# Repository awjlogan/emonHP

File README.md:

# emonHP - Heat Pump Monitoring

## Introduction

_emonHP_ is a system for monitoring heat pump operation. It is designed to work with [OpenEnergyMonitor](https://openenergymonitor.org), but can be used as a standalone system.

The system provides the following interfaces:

- MBUS
- RS485
- AC sense
- OneWire
- USB-C
- 40-pin Raspberry Pi header

## Getting started

### Getting a board

- Purchase a heat pump monitoring system from the [OpenEnergyMonitor Shop](https://shop.openenergymonitor.com/)
- Build your own!
  - With [KiCad](https://www.kicad.org/) installed, run `./generate.py` in the `pcb` directory (tested on Linux and macOS only) to generate manufacturing files (KiCad PCB, Gerbers, BoM).

### emonHP

> [!NOTE]
Setting up as an integrated emonHP system requires a Raspberry Pi 4. This exposes extra UART ports on the 40-pin header which are not available on older versions.

Connect the Raspberry Pi to the 40 pin header.

> [!WARNING]
Power must only be applied to one of the emonHP's USB-C port *or* the Raspberry Pi's power port, never both.

### Standalone

Connect to a host computer through the USB-C port. The emonHP will enumerate as 3 serial ports.

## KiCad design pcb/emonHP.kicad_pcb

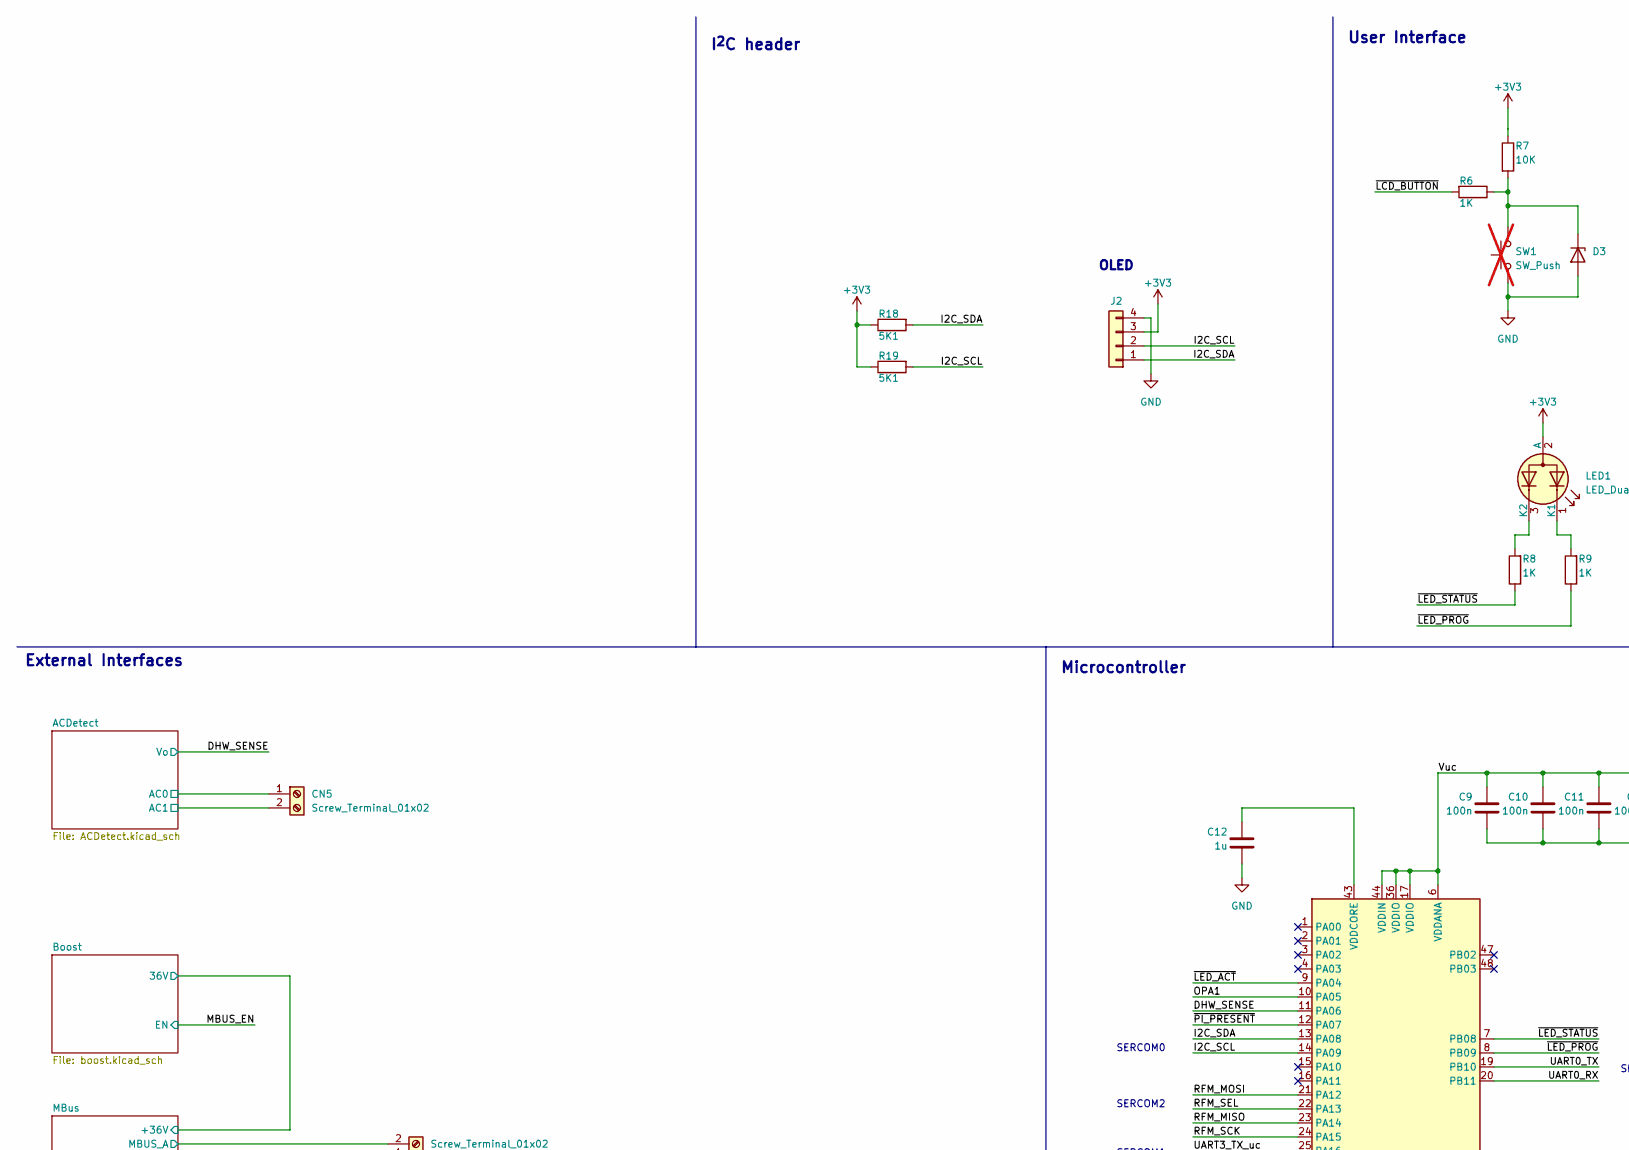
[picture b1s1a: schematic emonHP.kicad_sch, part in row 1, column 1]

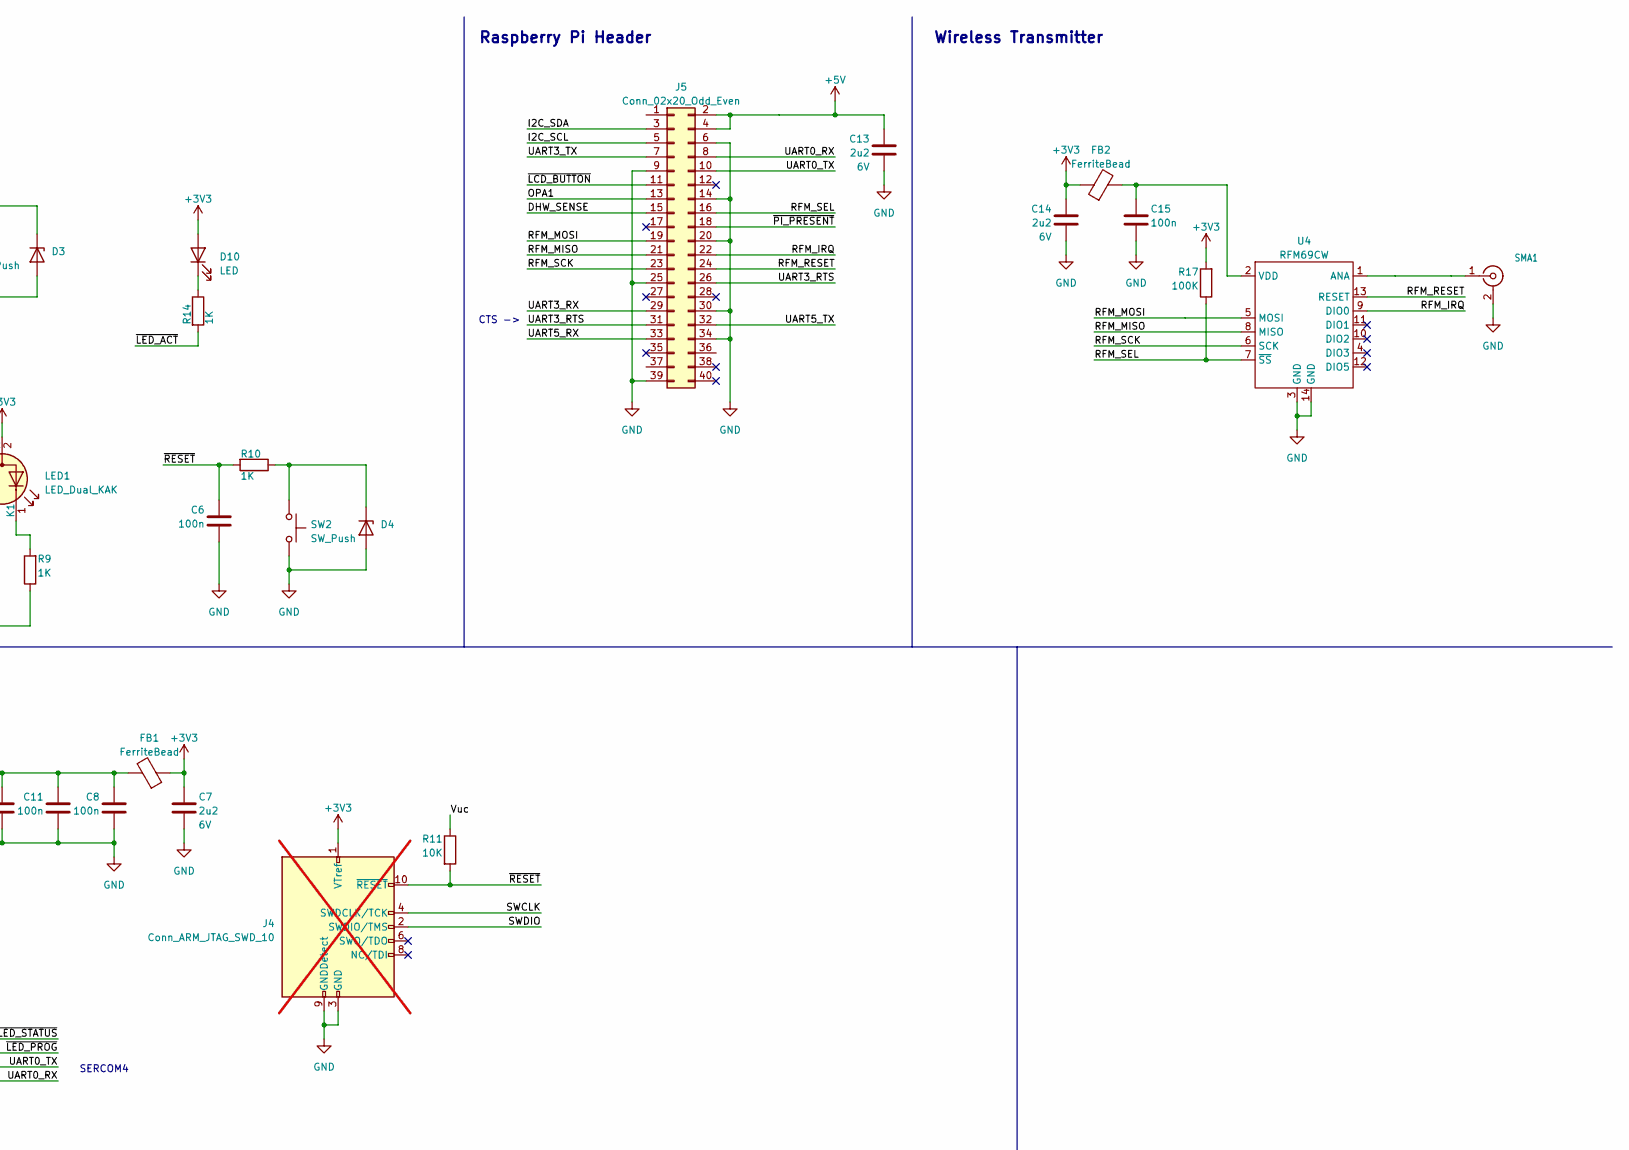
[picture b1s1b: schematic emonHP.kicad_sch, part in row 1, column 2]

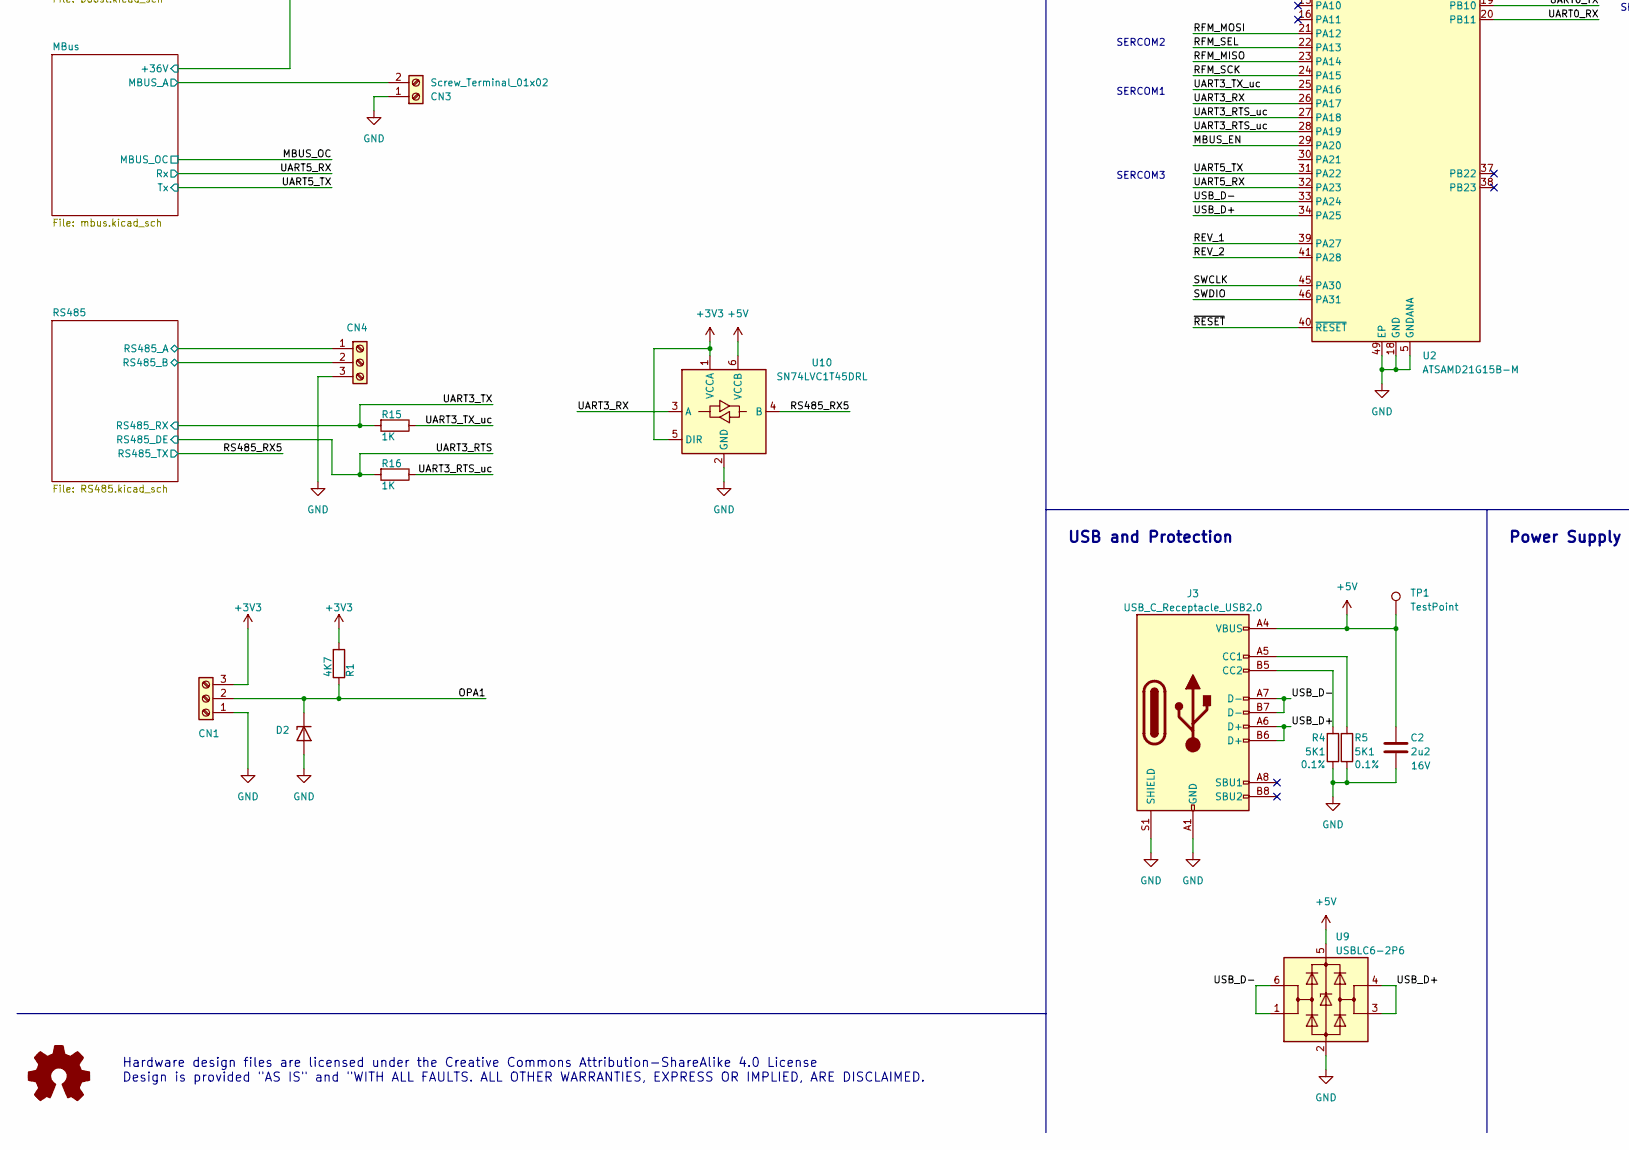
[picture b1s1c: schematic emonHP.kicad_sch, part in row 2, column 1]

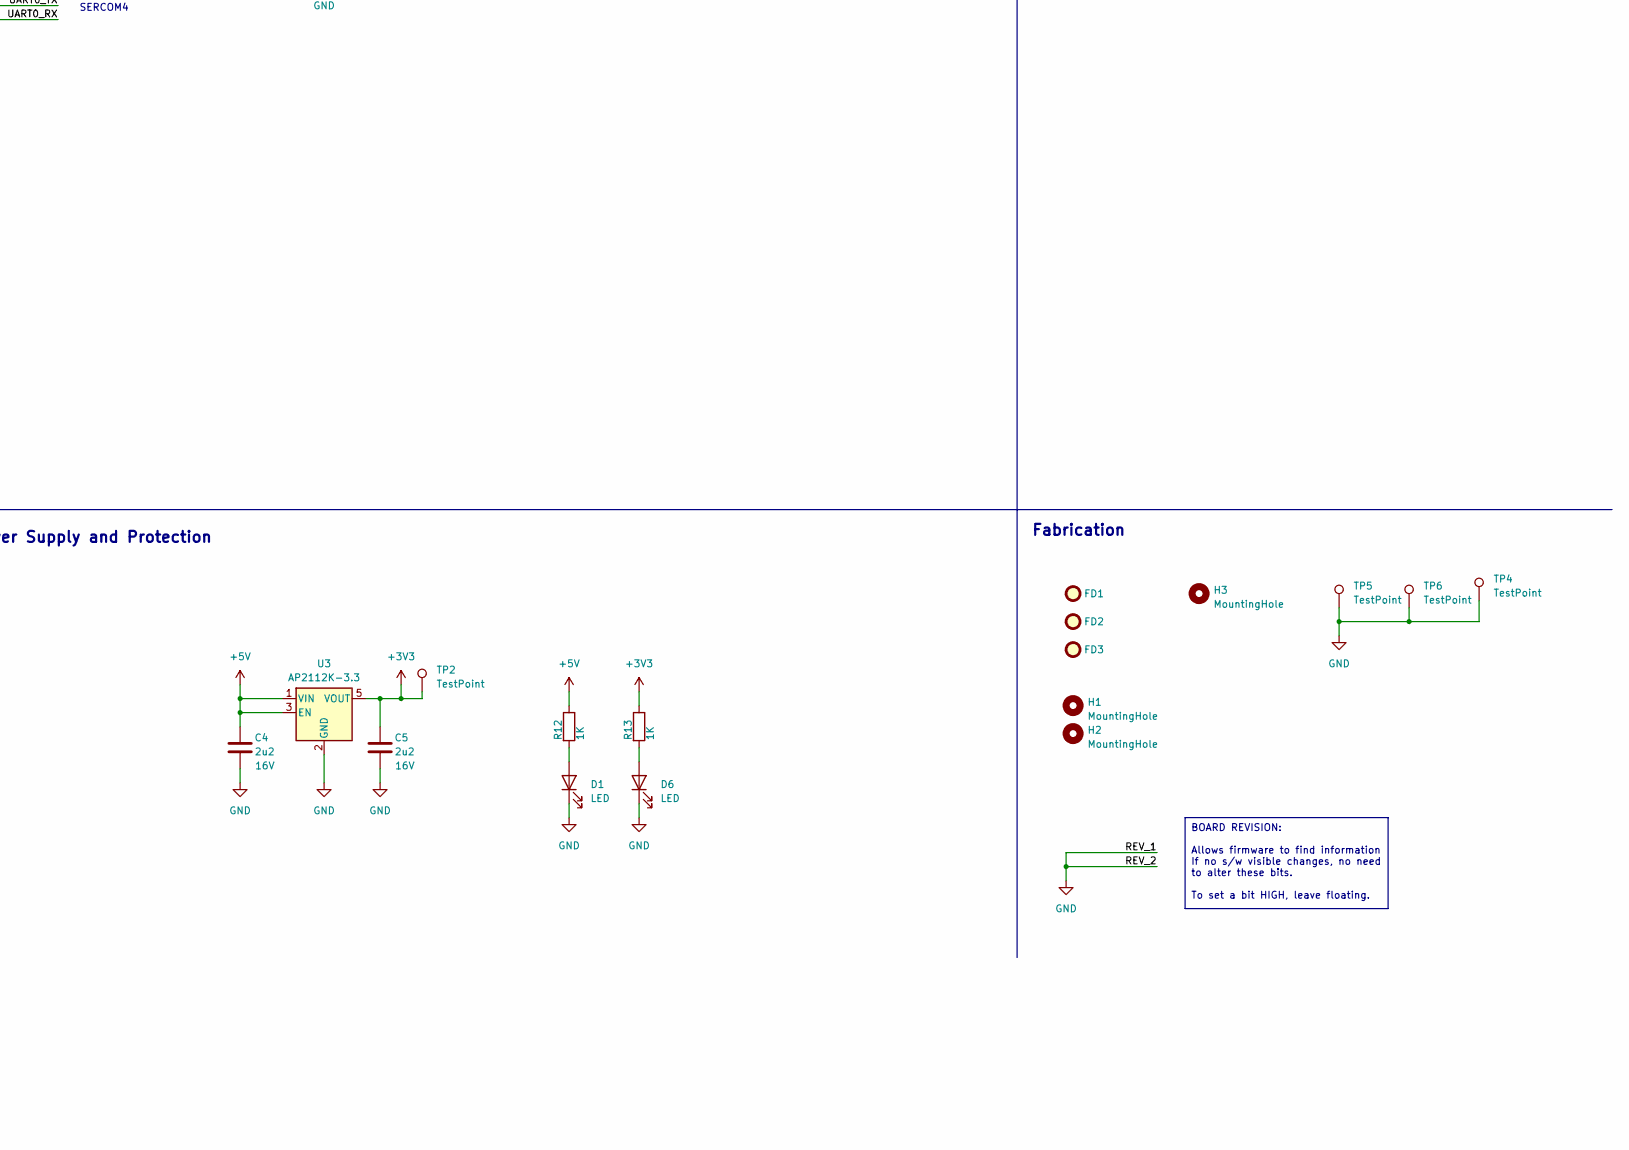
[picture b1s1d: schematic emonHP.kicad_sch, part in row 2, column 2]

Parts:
C2, C4, C5: 2u2; C_0603_1608Metric; Voltage 16V; LCSC C23630
C6, C8, C9, C10, C11, C15: 100n; C_0402_1005Metric; LCSC C1525
C7: 2u2; C_0603_1608Metric; Voltage 6V; LCSC C1525
C12: 1u; C_0402_1005Metric
C13, C14: 2u2; C_0603_1608Metric; Voltage 6V; LCSC C23630
CN1, CN4: CONN_03SCREW; TerminalBlock_Phoenix_PT-1,5-3-3.5-H_1x03_P3.50mm_Horizontal; MPN 5441359; Mouser 651-5441359
CN3: Screw_Terminal_01x02; TerminalBlock_Phoenix_PT-1,5-2-3.5-H_1x02_P3.50mm_Horizontal
CN5: Screw_Terminal_01x02; TerminalBlock_Phoenix_PT-1,5-2-5.0-H_1x02_P5.00mm_Horizontal
D1, D6, D10: LED; LED_0603_1608Metric; LCSC C2286
D2, D3, D4: ESD5Z3.3T5G; D_SOD-523
FB1, FB2: FerriteBead; R_0402_1005Metric
FD1, FD2, FD3: FIDUCIAL1X2; Fiducial_0.75mm_Mask1.5mm
H1, H2: MountingHole; MountingHole_2.7mm_M2.5
H3: MountingHole; MountingHole_2.1mm
J2: CONN_04PTH; PinSocket_1x04_P2.54mm_Vertical
J3: USB_C_Receptacle_USB2.0; CSP-USC16-TR; LCSC C27636760
J4: Conn_ARM_JTAG_SWD_10; PinHeader_2x05_P1.27mm_Vertical_SMD; not fitted
J5: Conn_02x20_Odd_Even; REF-182665
LED1: LED_Dual_KAK; LTST-S326; MPN LTST-S326KGJRKT; Mouser 859-LTST-S326KGJRKT
R1: 4K7; R_0402_1005Metric; LCSC C25905
R4, R5: 5K1; R_0402_1005Metric; Tolerance 0.1%; MPN ERA-3AED512V; Mouser 667-ERA-3AED512V
R6, R8, R9, R10, R12, R13, R14, R15, R16: 1K; R_0402_1005Metric; LCSC C11702
R7, R11: 10K; R_0402_1005Metric
R17: 100K; R_0402_1005Metric; LCSC C25741
R18, R19: 5K1; R_0402_1005Metric; LCSC C25905
SMA1: SMACONNECTOR; SMA_Amphenol_132203-12_Horizontal
SW1: SW_Push; SW_PUSH_6mm; not fitted
SW2: SW_Push; SW_Tactile_SPST_NO_Straight_CK_PTS636Sx25SMTRLFS
TP1, TP2, TP4, TP5, TP6: TestPoint; TestPoint_Pad_D1.0mm
U2: ATSAMD21G15B-M; QFN-48-1EP_7x7mm_P0.5mm_EP5.15x5.15mm; LCSC C1341309
U3: AP2112K-3.3; SOT-23-5; LCSC C51118
U4: RFM69CW
U9: USBLC6-2P6; SOT-666; MPN USBLC6-2P6; Mouser 511-USBLC6-2P6
U10: SN74LVC1T45DRL; SOT-563; LCSC C352970

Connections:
+3V3: C5.2, C7.1, C14.1, CN1.3, D10.2 (A), FB1.1, FB2.1, J2.3, J4.1 (VTref), LED1.2 (A), R1.2, R7.1, R13.1, R17.2, R18.1, R19.1, TP2.1, U3.5 (VOUT), U10.1 (VCCA), U10.5 (DIR); also elsewhere on the board
+5V: C2.2, C4.2, C13.1, J3.A4 (VBUS), J3.A9 (VBUS), J3.B4 (VBUS), J3.B9 (VBUS), J5.2, J5.4, R12.1, TP1.1, U3.1 (VIN), U3.3 (EN), U9.5 (VBUS), U10.6 (VCCB); also elsewhere on the board
/ACDetect/AC0: CN5.1; also elsewhere on the board
/ACDetect/AC1: CN5.2; also elsewhere on the board
/DHW_SENSE: J5.15, U2.11 (PA06); also elsewhere on the board
/I2C_SCL: J2.2, J5.5, R19.2, U2.14 (PA09)
/I2C_SDA: J2.1, J5.3, R18.2, U2.13 (PA08)
/MBUS_EN: U2.29 (PA20); also elsewhere on the board
/MBus/MBUS_A: CN3.2; also elsewhere on the board
/OPA1: CN1.2, D2.1 (K), J5.13, R1.1, U2.10 (PA05)
/RFM_IRQ: J5.22, U4.9 (DIO0)
/RFM_MISO: J5.21, U2.23 (PA14), U4.8 (MISO)
/RFM_MOSI: J5.19, U2.21 (PA12), U4.5 (MOSI)
/RFM_RESET: J5.24, U4.13 (RESET)
/RFM_SCK: J5.23, U2.24 (PA15), U4.6 (SCK)
/RFM_SEL: J5.16, R17.1, U2.22 (PA13), U4.7 (~SS)
/RS485/RS485_A: CN4.1; also elsewhere on the board
/RS485/RS485_B: CN4.2; also elsewhere on the board
/RS485_RX5: U10.4 (B); also elsewhere on the board
/SWCLK: J4.4 (SWDCLK/TCK), U2.45 (PA30)
/SWDIO: J4.2 (SWDIO/TMS), U2.46 (PA31)
/UART0_RX: J5.8, U2.20 (PB11)
/UART0_TX: J5.10, U2.19 (PB10)
/UART3_RTS: J5.26, J5.31, R16.2; also elsewhere on the board
/UART3_RTS_uc: R16.1, U2.27 (PA18), U2.28 (PA19)
/UART3_RX: J5.29, U2.26 (PA17), U10.3 (A)
/UART3_TX: J5.7, R15.2; also elsewhere on the board
/UART3_TX_uc: R15.1, U2.25 (PA16)
/UART5_RX: J5.33, U2.32 (PA23); also elsewhere on the board
/UART5_TX: J5.32, U2.31 (PA22); also elsewhere on the board
/USB_D+: J3.A6 (D+), J3.B6 (D+), U2.34 (PA25), U9.3 (I/O2), U9.4 (I/O2)
/USB_D-: J3.A7 (D-), J3.B7 (D-), U2.33 (PA24), U9.1 (I/O1), U9.6 (I/O1)
/Vuc: C8.1, C9.1, C10.1, C11.1, FB1.2, R11.1, U2.6 (VDDANA), U2.17 (VDDIO), U2.36 (VDDIO), U2.44 (VDDIN)
/~LCD_BUTTON: J5.11, R6.2
/~LED_ACT: R14.2, U2.9 (PA04)
/~LED_PROG: R9.1, U2.8 (PB09)
/~LED_STATUS: R8.1, U2.7 (PB08)
/~PI_PRESENT: J5.18, U2.12 (PA07)
/~RESET: C6.1, J4.10 (~RESET), R10.2, R11.2, U2.40 (~RESET)
GND: C2.1, C4.1, C5.1, C6.2, C7.2, C8.2, C9.2, C10.2, C11.2, C12.2, C13.2, C14.2, C15.2, CN1.1, CN3.1, CN4.3, D1.1 (K), D2.2 (A), D3.2 (A), D4.2 (A), D6.1 (K), J2.4, J3.A1 (GND), J3.A12 (GND), J3.B1 (GND), J3.B12 (GND), J3.S1 (SHIELD), J4.3 (GND), J4.5 (GND), J4.9 (GNDDetect), J5.6, J5.9, J5.14, J5.20, J5.25, J5.30, J5.34, J5.39, R4.1, R5.1, SMA1.2 (Ext), SW1.1, SW2.2, TP4.1, TP5.1, TP6.1, U2.5 (GNDANA), U2.18 (GND), U2.35 (GND), U2.39 (PA27), U2.41 (PA28), U2.42 (GND), U2.49 (EP), U3.2 (GND), U4.3 (GND), U4.14 (GND), U9.2 (GND), U10.2 (GND); also elsewhere on the board
unnamed: D1.2 (A), R12.2
unnamed: D3.1 (K), R6.1, R7.2, SW1.2
unnamed: D4.1 (K), R10.1, SW2.1
unnamed: D6.2 (A), R13.2
unnamed: D10.1 (K), R14.1
unnamed: J3.A5 (CC1), R5.2
unnamed: J3.B5 (CC2), R4.2
unnamed: LED1.1 (K1), R9.2
unnamed: LED1.3 (K2), R8.2
unnamed: SMA1.1 (In), U4.1 (ANA)
unnamed: C12.1, U2.43 (VDDCORE)
unnamed: C15.1, FB2.2, U4.2 (VDD)

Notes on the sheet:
BOARD REVISION: Allows firmware to find information If no s/w visible changes, no need to alter these bits. To set a bit HIGH, leave floating.
Raspberry Pi Header
Power Supply and Protection
SERCOM1
CTS ->
Hardware design files are licensed under the Creative Commons Attribution-ShareAlike 4.0 License Design is provided "AS IS" and "WITH ALL FAULTS. ALL OTHER WARRANTIES, EXPRESS OR IMPLIED, ARE DISCLAIMED.
Microcontroller
SERCOM4
User Interface
SERCOM0
SERCOM3
USB and Protection
SERCOM2
Fabrication
OLED
External Interfaces
I^{2}C header
Wireless Transmitter

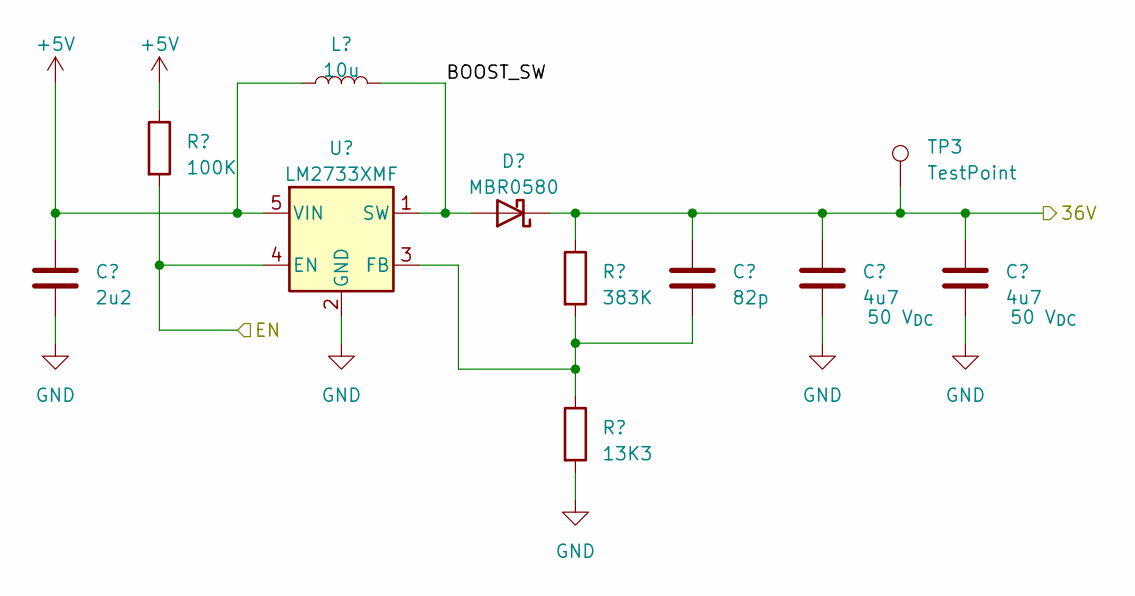
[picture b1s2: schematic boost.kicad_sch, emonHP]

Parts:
C18: 2u2; C_0603_1608Metric; LCSC C23630
C19: 82p; C_0603_1608Metric; LCSC C1683
C20, C21: 4u7; C_0805_2012Metric; Voltage 50 V_{DC}; MPN GRM21BZ71H475ME15L; LCSC C23630
D7: MBR0580; D_SOD-123; LCSC C177047
L1: 10u; L_Abracon_ASPI-3012S; MPN ASPI-3012S-100M-T; Mouser 815-ASPI-3012S-100MT
R26: 100K; R_0402_1005Metric; LCSC C25741
R27: 383K; R_0402_1005Metric; LCSC C25557
R28: 13K3; R_0402_1005Metric; LCSC C122547
TP3: TestPoint; TestPoint_Pad_D1.0mm
U5: LM2733XMF; SOT-23-5; MPN LM2733XMFX/NOPB; Mouser 926-LM2733XMFX/NOPB

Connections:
+5V: C18.1, L1.2, R26.1, U5.5 (VIN); also elsewhere on the board
/Boost/BOOST_SW: D7.2 (A), L1.1, U5.1 (SW)
/MBUS_EN: R26.2, U5.4 (EN); also elsewhere on the board
/MBus/36V: C19.1, C20.1, C21.1, D7.1 (K), R27.1, TP3.1; also elsewhere on the board
GND: C18.2, C20.2, C21.2, R28.2, U5.2 (GND); also elsewhere on the board
unnamed: C19.2, R27.2, R28.1, U5.3 (FB)

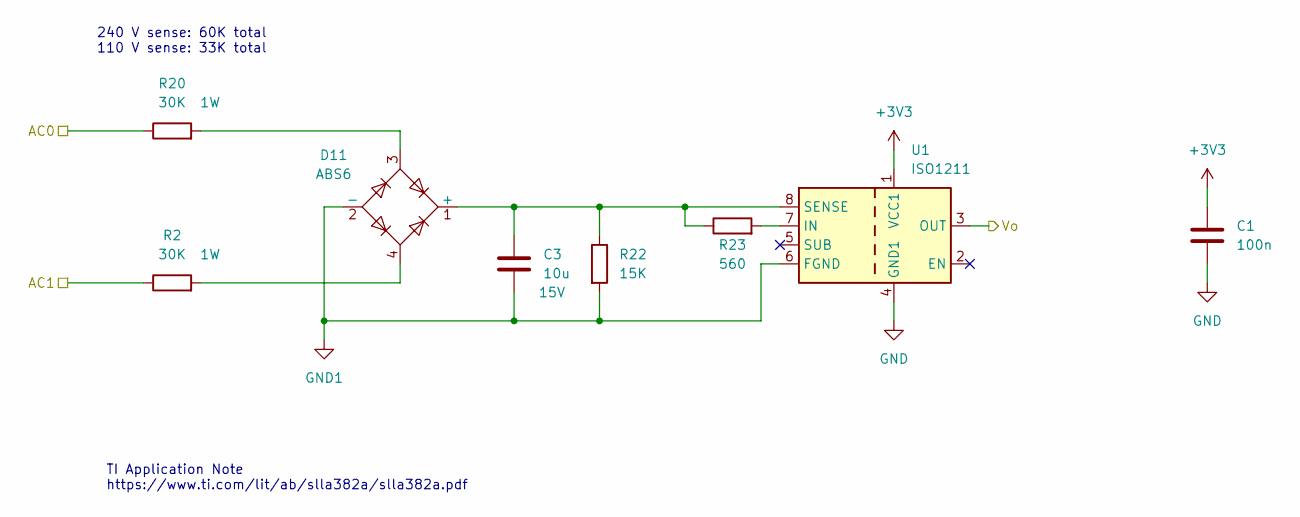
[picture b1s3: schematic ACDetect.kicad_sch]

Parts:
C1: 100n; C_0402_1005Metric; LCSC C1525
C3: 10u; C_0603_1608Metric; Voltage 15V
D11: ABS6; Diode_Bridge_Diotec_ABS; LCSC C353567
R2, R20: 30K; R_2512_6332Metric; MPN CRCW251230K0JNEG
R22: 15K; R_0603_1608Metric; LCSC C22809
R23: 560; R_0603_1608Metric; LCSC C23204
U1: ISO1211; SOIC-8_3.9x4.9mm_P1.27mm; LCSC C2674102

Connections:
+3V3: C1.1, U1.1 (VCC1); also elsewhere on the board
/ACDetect/AC0: R20.1; also elsewhere on the board
/ACDetect/AC1: R2.1; also elsewhere on the board
/DHW_SENSE: U1.3 (OUT); also elsewhere on the board
GND: C1.2, U1.4 (GND1); also elsewhere on the board
GND1: C3.2, D11.2 (-), R22.2, U1.6 (FGND)
unnamed: C3.1, D11.1 (+), R22.1, R23.1, U1.8 (SENSE)
unnamed: D11.3, R20.2
unnamed: D11.4, R2.2
unnamed: R23.2, U1.7 (IN)

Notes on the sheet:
240 V sense: 60K total 110 V sense: 33K total
TI Application Note https://www.ti.com/lit/ab/slla382a/slla382a.pdf

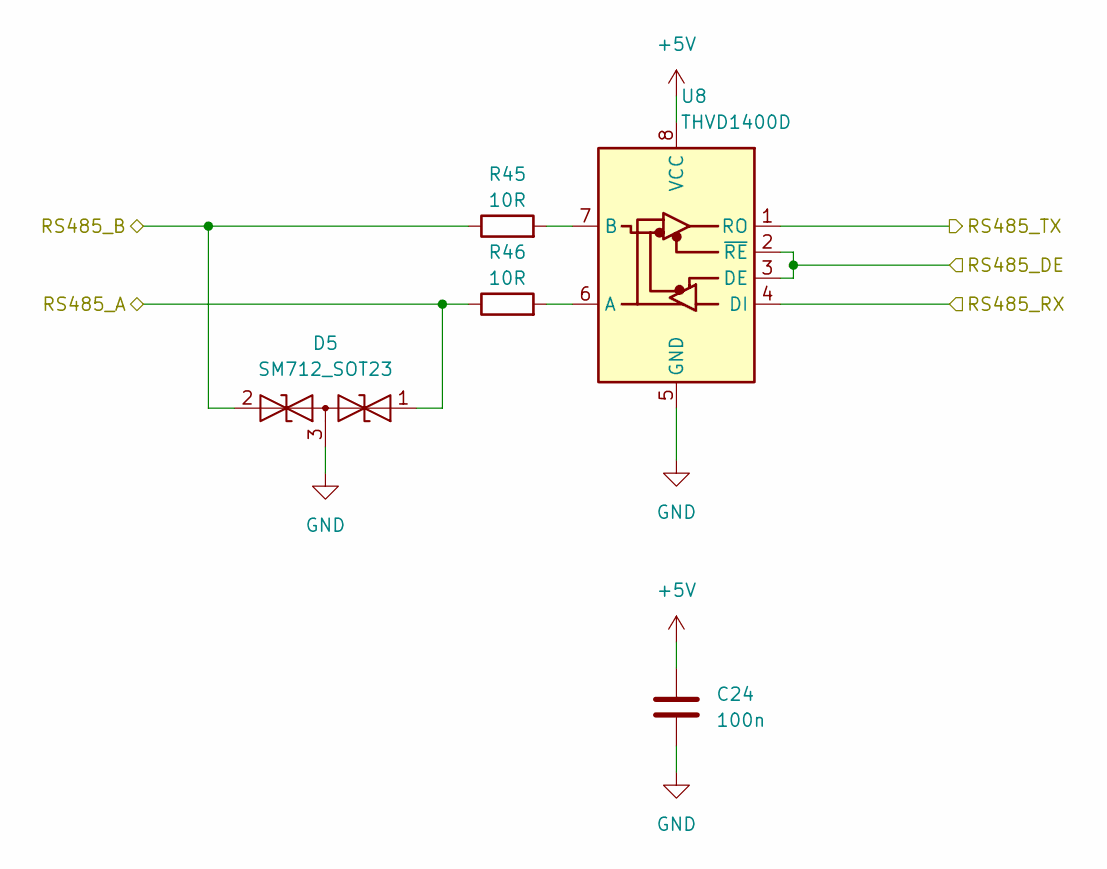
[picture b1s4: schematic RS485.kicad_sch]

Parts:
C24: 100n; C_0402_1005Metric; LCSC C1525
D5: SM712_SOT23; SOT-23; LCSC C172881
R45, R46: 10R; R_0603_1608Metric
U8: THVD1400D; SOIC-8_3.9x4.9mm_P1.27mm; LCSC C3235232

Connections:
+5V: C24.1, U8.8 (VCC); also elsewhere on the board
/RS485/RS485_A: D5.1 (A1), R46.1; also elsewhere on the board
/RS485/RS485_B: D5.2 (A2), R45.1; also elsewhere on the board
/RS485_RX5: U8.1 (RO); also elsewhere on the board
/UART3_RTS: U8.2 (~RE), U8.3 (DE); also elsewhere on the board
/UART3_TX: U8.4 (DI); also elsewhere on the board
GND: C24.2, D5.3 (common), U8.5 (GND); also elsewhere on the board
unnamed: R46.2, U8.6 (A)
unnamed: R45.2, U8.7 (B)

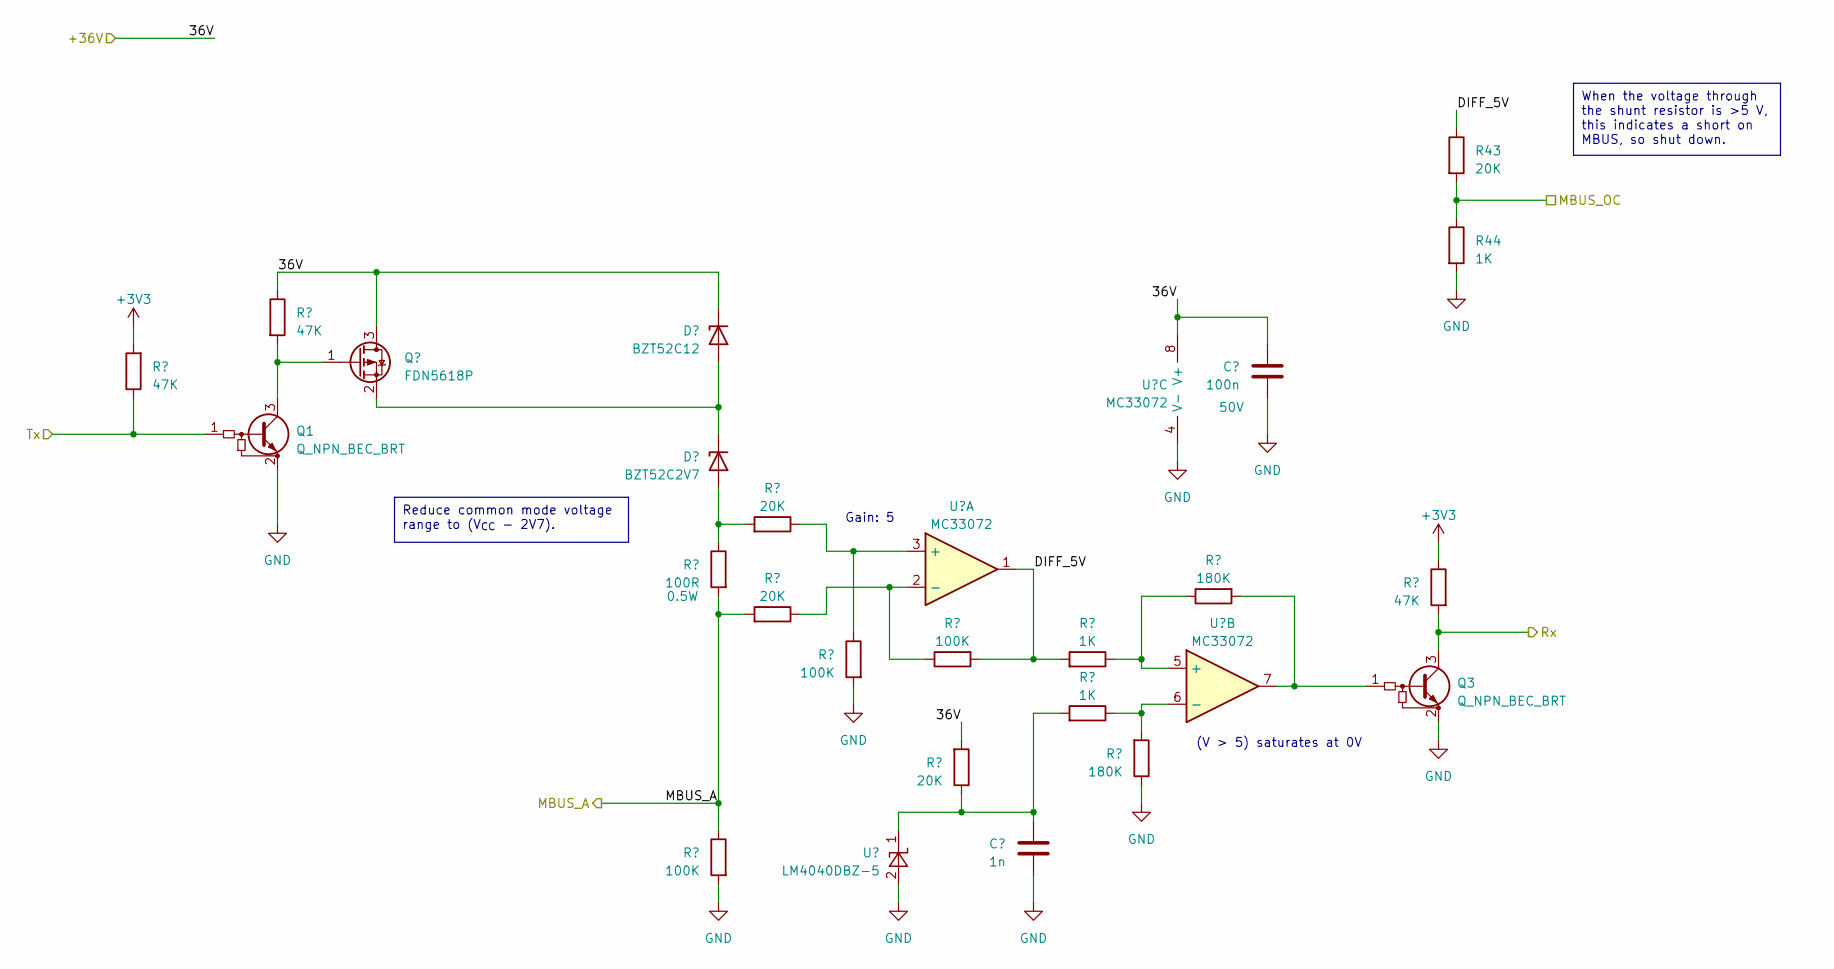
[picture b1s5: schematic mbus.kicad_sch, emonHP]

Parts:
C22: 1n; C_0402_1005Metric
C23: 100n; C_0402_1005Metric; Voltage 50V; LCSC C307331
D8: BZT52C12; D_SOD-123F; LCSC C124196
D9: BZT52C2V7; D_SOD-123F; LCSC C5244698
Q1, Q3: Q_NPN_BEC_BRT; SOT-23
Q2: FDN5618P; SOT-23; LCSC C400792
R29, R30, R42: 47K; R_0402_1005Metric
R31: 100R; R_0805_2012Metric; MPN ERJ-P06J101V; Mouser 667-ERJ-P06J101V
R32, R35, R36: 100K; R_0402_1005Metric; LCSC C25741
R33, R34, R37, R43: 20K; R_0402_1005Metric; LCSC C25765
R38, R39, R44: 1K; R_0402_1005Metric; LCSC C11702
R40, R41: 180K; R_0402_1005Metric; LCSC C25760
U6: LM4040DBZ-5; SOT-23; MPN LM4040DYM3-5.0-TR; Mouser 998-LM4040DYM3-5.0TR
U7: MC33072; SOIC-8_3.9x4.9mm_P1.27mm; MPN MC33072DR2G; Mouser 863-MC33072DR2G

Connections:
+3V3: R29.2, R42.1; also elsewhere on the board
/MBUS_OC: R43.2, R44.1
/MBus/36V: C23.1, D8.1 (K), Q2.3 (D), R30.1, R37.2, U7.8 (V+); also elsewhere on the board
/MBus/DIFF_5V: R36.2, R38.2, R43.1, U7.1
/MBus/MBUS_A: R31.2, R32.1, R34.2; also elsewhere on the board
/UART5_RX: Q3.3 (C), R42.2; also elsewhere on the board
/UART5_TX: Q1.1 (B), R29.1; also elsewhere on the board
GND: C22.2, C23.2, Q1.2 (E), Q3.2 (E), R32.2, R35.2, R40.1, R44.2, U6.2 (A), U7.4 (V-); also elsewhere on the board
unnamed: D8.2 (A), D9.1 (K), Q2.2 (S)
unnamed: D9.2 (A), R31.1, R33.2
unnamed: Q1.3 (C), Q2.1 (G), R30.2
unnamed: Q3.1 (B), R41.2, U7.7
unnamed: C22.1, R37.1, R39.2, U6.1 (K)
unnamed: R33.1, R35.1, U7.3 (+)
unnamed: R34.1, R36.1, U7.2 (-)
unnamed: R38.1, R41.1, U7.5 (+)
unnamed: R39.1, R40.2, U7.6 (-)

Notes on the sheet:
When the voltage through the shunt resistor is >5 V, this indicates a short on MBUS, so shut down.
Reduce common mode voltage range to (V_{CC} - 2V7).
Gain: 5
(V > 5) saturates at 0V

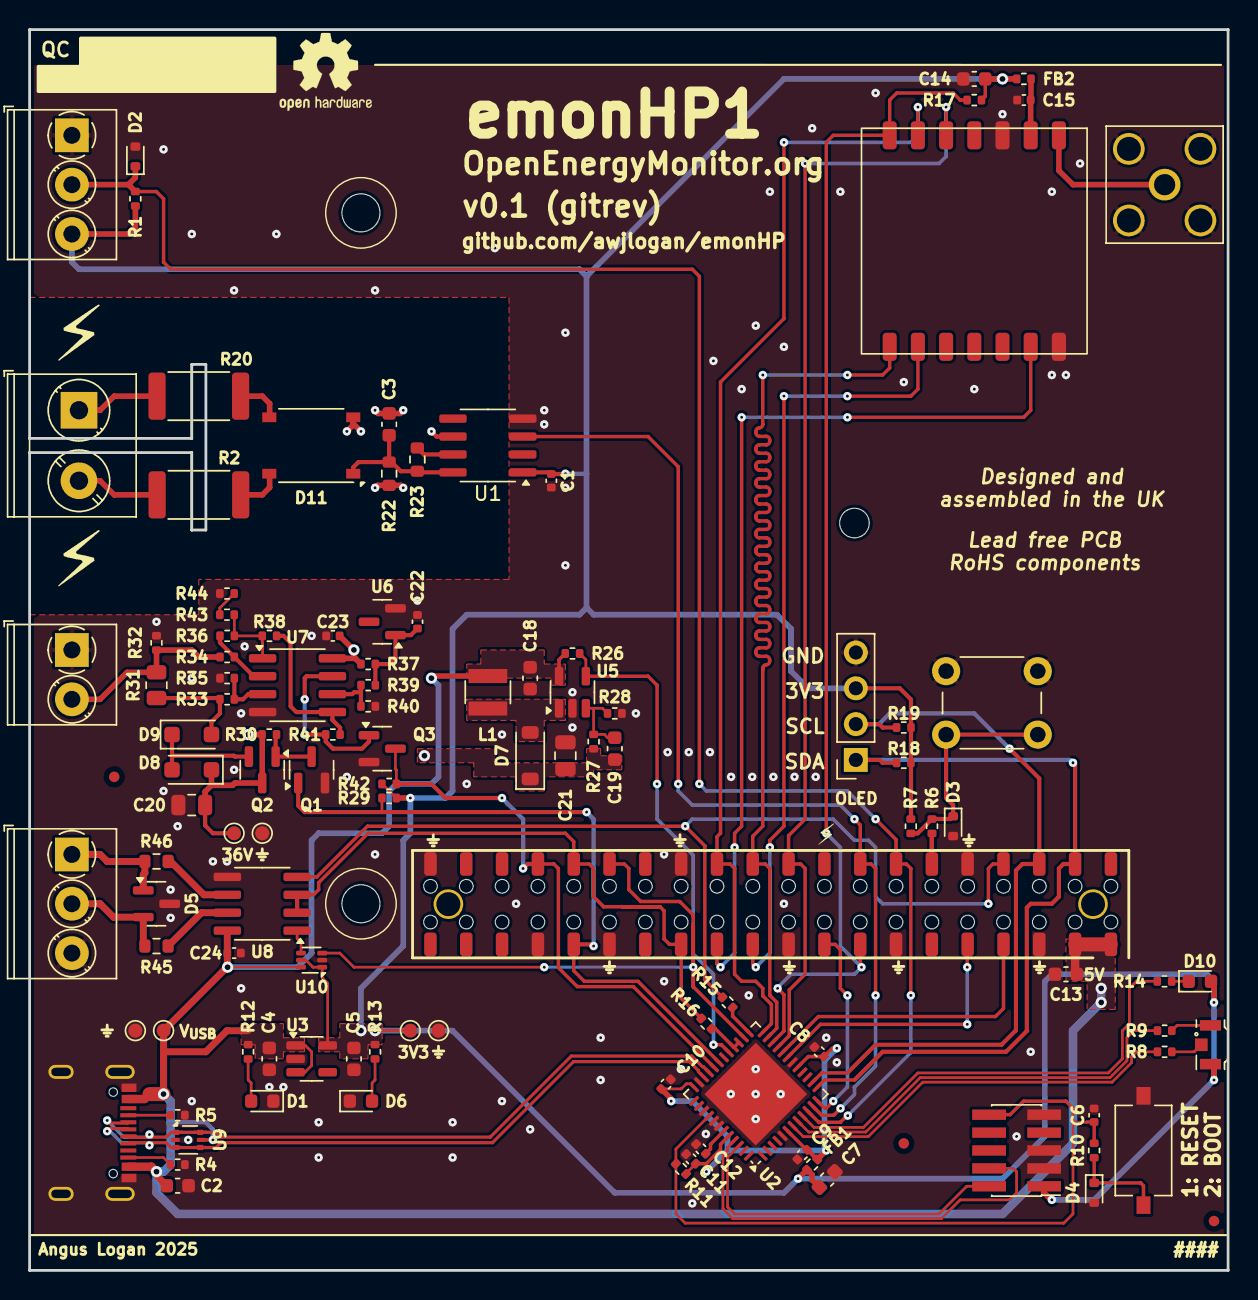
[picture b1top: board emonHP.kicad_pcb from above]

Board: 4 copper layers, 85.0 x 88.0 mm, 115 parts (0 on the bottom side), 73 nets.

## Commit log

2024-06-11 * Initial commit!
2024-07-04 * Continue initial placement
    - External connectors added
    - Switch and indicator LED added
2024-07-28 * Work in progress
    - Add generate script
    - Add switch model
    - Start routing
    - Tidy schematic
2024-08-11 * [0.1-dev] Voltage good
    - Add 36V voltage good detection
    - Add all 3D models
    - Correct footprint for front LED
2024-08-11 * [0.1-dev] Add git commit references and README
2024-08-14 * Swap reset button for cheap onboard
    - Can access bootloader from serial, no need for front panel
2025-05-23 [v0.1-dev] First pass on emonPi format
2025-05-26 Move SAMD below, reroute
2025-06-02 Swap 1Wire and AC sense
